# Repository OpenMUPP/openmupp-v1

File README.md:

# OpenMUPP v1 probe board

OpenMUPP v1 is a multi-protocol programming and debug probe.
The design is open hardware.
The board name is `OpenMUPP v1`.
The KiCad 10 project is in this repository.

## What the board does

- It runs **USB CDC, CMSIS-DAP v2 and EDBG (AVR) at the same time** in one firmware image.
- It transfers data **faster than the original Versaloon Mini**. The core runs at 144 MHz, and USB runs at high speed (480 Mbit/s).
- It connects to targets from **1.2 V to 5 V** through level shifters. A 1.2 V target is limited to about 5 MHz.
- It supplies the target with **3.3 V or 5 V (up to about 300 mA)**.
- It makes an adjustable **VPP of 5 V to 14 V** for high-voltage programming of AVR and PIC parts.
- It has **one target connector (J4)**. An adapter board plugs onto J4 and maps it to each target pinout.

## Hardware overview

```mermaid
flowchart LR
    usb["USB-C (J1)"] --> fuse["Polyfuse F1<br/>1.1 A<br/>+5V"]
    fuse --> ldo["3.3 V LDO"]
    fuse --> boost["Boost (U13)<br/>5 V to 14 V"]
    ldo --> mcu["CH32V307RCT6 (U2)<br/>3.3 V"]
    mcu <--> ls["Level shifters<br/>U3 to U6"]
    ls --> esd["33 Ω series resistors<br/>and ESD diodes"]
    esd --> j4["Target connector J4<br/>2 × 10, 2.54 mm"]

    ldo --> tps33["3.3 V target switch<br/>TPS2553 (U12)"]
    fuse --> tps5["5 V target switch<br/>TPS2553 (U14)"]
    tps33 --> vtref(("VTREF"))
    tps5 --> vtref
    vtref --> j4

    boost --> vpp["VPP switch<br/>P-FET (Q2)"]
    vpp --> j4
    pd["Pin 19 pull-down<br/>N-FET (Q6), pull-up to VTREF"] --> j4

    mcu -- "TARGET_PWR_EN" --> tps33
    mcu -- "TARGET_5V_EN" --> tps5
    mcu -- "VPP_12V_ADJ<br/>(DAC: 5 V to 14 V)" --> boost
    mcu -- "VPP_EN, VPP_ON" --> vpp
    mcu -- "VPP_PD" --> pd
    boost -- "VPP_SENSE" --> mcu
```

| Block | Part | Notes |
|-------|------|-------|
| MCU | CH32V307RCT6, LQFP64 (U2) | QingKe V4F RISC-V, 144 MHz, 256 KB flash, 64 KB SRAM. 8 MHz crystal (Y1). |
| USB | USB-C receptacle (J1), USBLC6-2SC6 (U1) | USB 2.0 high speed (USBHS on PB6, PB7). 5.1 kΩ CC resistors. |
| 3.3 V rail | XC6220B331MR-G LDO | Supplies the MCU and the target power switch. |
| VBUS protection | 1.1 A polyfuse (F1), 2.2 A trip, 16 V | At 4.75 V VBUS, expect `+5V` at about 4.6 V or more at full load. See [Target power](docs/hardware.md#target-power). |
| Target power (3.3 V or 5 V) | TPS2553 (U12, 3.3 V), TPS2553 (U14, 5 V), FDV301N interlock (Q4) | Current limit about 300 mA (ILIM 91 kΩ) on each rail. Both outputs join `VTREF`. See [Target power](docs/hardware.md#target-power). |
| VPP (5 V to 14 V) | MT3608 boost (U13), AO3401A P-FET (Q2), FDV301N driver (Q3), MMBT3906 current limit (Q5), FDV301N pull-down (Q6) | The firmware sets the level with the DAC on PA5 (`VPP_12V_ADJ`). Current limit about 17 mA. Pin 19 has three states: 0 V, `VTREF` and VPP. See [High voltage (VPP)](docs/hardware.md#high-voltage-vpp). |
| Level shifters | SN74LXC8T245 (U3, U4), SN74LXC1T45 (U5, U6) | All parts work from 1.1 V to 5.5 V. |
| Reset path | FDV301N (Q1), U4 channel 4 | Q1 pulls nRESET low. U4 reads the line back. |
| ESD | TPD4E05U06 (U8 to U10) | On all J4 signals except the supplies. |
| Probe debug | J3 (5-pin SWD), J2 (4-pin UART) | J3 debugs the probe MCU only. J2 is the log port of the probe firmware. **They are not target connectors.** |
| User I/O | SW1 (key and BOOT0), LEDs D1 (blue) and D4 (red) for state, D2 (green) for USB | |

### Target connector J4

J4 is a 2 × 10 IDC header, 2.54 mm. The footprint in the schematic is `Connector_IDC:IDC-Header_2x10_P2.54mm_Horizontal`. Use a shrouded and keyed header. VPP is on pin 19, so a shifted plug must not fit.

| Pin | Signal | Pin | Signal |
|-----|--------|-----|--------|
| 1 | `VTREF`: target voltage sense, and target supply when the probe powers the target | 2 | Reserved (no connect) |
| 3 | GND | 4 | TMS / SWDIO / data (`DIR_SWDIO`) |
| 5 | GND | 6 | TCK / SWCLK / SCK |
| 7 | GND | 8 | TDO / SWO / MISO |
| 9 | GND | 10 | TDI / MOSI |
| 11 | RTCK | 12 | nRESET / debugWIRE, open-drain |
| 13 | UART TX (probe output) | 14 | UART RX (probe input) |
| 15 | TRST | 16 | Adapter ID (ADC, 3.3 V domain) |
| 17 | `AUX1` | 18 | `AUX2` |
| 19 | VPP (0 V, `VTREF`, or 5 V to 14 V) | 20 | GND |

- **Target power is on pin 1.** One pin carries the sense and the supply. The limit is about 300 mA at 3.3 V and at 5 V.
- **Pin 2 is reserved.** A later adapter that needs a second supply pin can use it, with its own switch.
- **Pin 16 goes to the adapter only.** It never goes to the target.

### Adapter boards and adapter ID

An adapter board has connectors, wires and one ID resistor. The resistor goes from J4 pin 16 to GND. R30 (10 kΩ) pulls pin 16 up to 3.3 V. The firmware reads the ratio x = R<sub>ID</sub> / (R<sub>ID</sub> + 10 kΩ) on PB1. The ADC reference and R30 share the 3.3 V rail, so supply drift cancels. R44 (10 kΩ) in series and D5 (BAT54 Schottky diode) to 3.3 V protect PB1 (net `ADAPTER_ID_MCU`). They work when a 5 V target supply is on pin 16 by mistake. C13 (100 nF) from `ADAPTER_ID_MCU` to GND filters the ADC input. The firmware must use a long ADC sample time and keep the internal pull resistors off.

The AVR 10-pin connector uses the Atmel-ICE pinout. Three passive variants route the data pin to SWDIO:

| Variant | Protocols | Slot |
|---------|-----------|------|
| A | JTAG, ISP, debugWIRE | 1 |
| B | PDI | 2 |
| C | TPI, aWire | 3 |

UPDI does not use SWDIO. It uses J4 pin 12 (nRESET), because the 2.2 kΩ pull-up on SWDIO is too strong for the UPDI pin of the target. See [adapters/README.md](adapters/README.md#updi-on-j4-pin-12). A UPDI adapter variant for the Atmel-ICE 10-pin connector has no slot yet.

| Slot | R<sub>ID</sub> (E24, 1 %) | x | Accept window | Use |
|------|------------------|-------|---------------|-----|
| — | 0 Ω (short) | 0.000 | below 0.05 | Fault: pin 16 shorted to GND |
| 1 | 1.1 kΩ | 0.099 | 0.05 to 0.15 | Variant A |
| 2 | 2.4 kΩ | 0.194 | 0.15 to 0.25 | Variant B |
| 3 | 4.3 kΩ | 0.301 | 0.25 to 0.35 | Variant C |
| 4 | 6.8 kΩ | 0.405 | 0.35 to 0.45 | Arm adapter |
| 5 | 10 kΩ | 0.500 | 0.45 to 0.55 | Pin-header adapter |
| 6 | 15 kΩ | 0.600 | 0.55 to 0.65 | Free |
| 7 | 24 kΩ | 0.706 | 0.65 to 0.75 | Free |
| 8 | 39 kΩ | 0.796 | 0.75 to 0.85 | AVR high-voltage adapter |
| 9 | 91 kΩ | 0.901 | 0.85 to 0.95 | PIC high-voltage adapter |
| — | open | 1.000 | above 0.95 | No adapter |

The worst-case error is about 0.007 in x, and the windows are ±0.05 wide. The firmware treats a free slot as "unknown adapter". The firmware enables VPP only for slots 8 and 9.

The adapter schematics are in [adapters/](adapters/README.md). Each adapter has a female 2 × 10 header that plugs directly onto J4. No ribbon cable is necessary.

See [docs/hardware.md](docs/hardware.md) for the sheets, level shifting, target power, VPP and the MCU pin map.

## Firmware

The firmware is the `openmupp` project. The CH32V307 has a ROM bootloader. It can program the flash through USB (WCH ISP protocol). The bootloader can also use USART1 (PA9, PA10), but on this board these pins drive LEDs and have no connector. Hold SW1 (BOOT0) during reset to start it. The firmware port to the CH32V307 is in progress. A firmware jump to the bootloader is not available yet.

Related repositories:

- Firmware: <https://github.com/OpenMUPP/openmupp>
- Drivers: <https://github.com/armint/ch32v00x-system> and <https://github.com/armint/ch32v00x-art>

## Getting started

### Requirements

- KiCad 10.0.6 or newer.
- The shared footprint libraries. They are not public. The PCB file has a copy of each footprint, so you can open and edit the board without them. The project uses the nicknames `resistors`, `capacitors`, `headers`, `connectors`, `inductors` and `sot`. The stock KiCad libraries (`Package_*`, `Connector_IDC`, `Diode_SMD`, `LED_SMD`, `Crystal`, `Fuse`, `Button_Switch_SMD`) must also be present.

### Open the project

1. Clone this repository.
2. Open `openmupp-v1.kicad_pro`.

The board and the schematic open without the shared footprint libraries. To change a footprint, edit the copy in the PCB file.

The project symbol library `openmupp-v1` is in the repository. `sym-lib-table` links it with `${KIPRJMOD}`.

### Conventions

- **Reference designators are unique across all sheets.** Check before you add a part.
- **Every part has an `LCSC` field** for JLCPCB assembly. Prefer parts from the JLCPCB basic library. Each extended part costs a setup fee.
- **Small N-FETs:** use the FDV301N (LCSC C15310). V<sub>GS(th)</sub> is 1.06 V maximum, so a gate drive of 1.8 V turns it on. The limits are 25 V V<sub>DS</sub> and 8 V V<sub>GS</sub>.
- **Footprints:** check the pads against the datasheet land pattern.
- **Checks:** run ERC after each change. Look for shorted nets and for unconnected pins.

## License

Copyright Armin van der Togt 2026.

This design is licensed under the CERN Open Hardware Licence Version 2 - Strongly Reciprocal (CERN-OHL-S-2.0). See [LICENSE](LICENSE).
The design has no warranty. Refer to the licence for the applicable conditions.

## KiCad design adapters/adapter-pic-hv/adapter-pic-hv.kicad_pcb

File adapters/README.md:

# Target adapters for OpenMUPP v1

Each folder is a KiCad 10 project with the schematic and the board layout of one target adapter.

| Folder                                     | Adapter          | Slot | R<sub>ID</sub> | Target connectors                                              |
|--------------------------------------------|------------------|------|----------------|----------------------------------------------------------------|
| [adapter-avr-jtag-isp](adapter-avr-jtag-isp/) | AVR variant A | 1 | 1.1 kΩ | Atmel-ICE 10 (1.27 mm), AVR JTAG 10 (2.54 mm), 2 × 3 ISP |
| [adapter-arm](adapter-arm/)                | Arm              | 4    | 6.8 kΩ         | ARM JTAG 20, Cortex Debug 10, STDC14                           |
| [adapter-pin-header](adapter-pin-header/)  | Pin header       | 5    | 10 kΩ          | 1 × 6 SWD / CH32 / SWIM, 1 × 4 ST SWIM, 2 × 5 WCH-LinkE layout |
| [adapter-avr-hv](adapter-avr-hv/)          | AVR high voltage | 8    | 39 kΩ          | DIP-8 and DIP-14 sockets (HVSP), 2 × 3 TPI and UPDI            |
| [adapter-pic-hv](adapter-pic-hv/)          | PIC high voltage | 9    | 91 kΩ          | PICkit ICSP 1 × 6                                              |

The slot table and the J4 pinout are in the [main README](../README.md#adapter-boards-and-adapter-id).

## Rules for all adapters

1. J1 is a female 2 × 10 header, 2.54 mm. It plugs directly onto J4 of the probe. The pin numbers of J1 are the J4 pin numbers.
2. One 1 % resistor (R1) goes from J1 pin 16 to GND. J1 pin 16 never goes to the target.
3. J1 pin 2 (reserved) stays open. J1 pin 19 (VPP) stays open on each adapter that is not a high-voltage adapter.
4. Each adapter has a 1 × 4 debug UART header (J5): 1 GND, 2 RX (probe input), 3 TX (probe output), 4 `VTREF`. The labels are from the probe side. Pins 1 to 3 have the same order as J2 on the main board. Pin 4 lets the UART work without a debug connector to the target.
5. Connect only one target connector at a time.

## Female header on J4

J4 on the probe is a shrouded, right-angle header (`IDC-Header_2x10_P2.54mm_Horizontal`). The adapter boards use `PinSocket_2x10_P2.54mm_Horizontal` for J1, so the adapter board is in the same plane as the probe. Check these items before you order the boards:

- **Fit.** The socket body must go into the shroud of J4. Measure the shroud opening and the socket body.
- **Pin mirror.** The socket and the header mate face to face. Make sure that J1 pin 1 touches J4 pin 1 in the layout.
- **Polarity.** A plain socket has no key, so it can go in rotated by 180°. Then J1 pin 16 touches a probe GND pin, and the probe pin 16 touches an adapter GND pin. The adapter ID reads 0 Ω (the fault slot). The firmware must then keep the shifter outputs, the target power and VPP off. Use a keyed socket, or add a mechanical key on the adapter board, if possible.

## RESET and MCLR on J4 pin 19

`adapter-avr-hv` and `adapter-pic-hv` connect the target RESET or MCLR pin directly to J1 pin 19. The nets are `RESET_VPP` and `MCLR_VPP`. The probe gives pin 19 three levels: 0 V (reset), `VTREF` (run) and VPP (program). See [Pin 19 states](../docs/hardware.md#pin-19-states). Thus the adapters have no reset circuit, and J1 pin 18 (`AUX2`) is not used.

HVSP entry needs RESET at 0 V while `VCC` comes up. Then RESET must go to 12 V after a short time. Q6 on the probe holds pin 19 at 0 V. The firmware can set `VPP_ON` before `VCC` comes up, because Q6 holds pin 19 low against the current limit. Then the firmware releases Q6 at the time that the data sheet gives. Pin 19 then goes to VPP in some µs.

## UPDI on J4 pin 12

UPDI uses J4 pin 12 (nRESET / debugWIRE), not J4 pin 4 (SWDIO). The reasons:

- The UPDI pin of a tinyAVR is a weak driver. The ATtiny1614/16/17 data sheet (DS40002204A, table 36-16, VOL2) guarantees only 0.1 mA at 1.8 V and 0.5 mA at 5 V.
- J4 pin 4 has a 2.2 kΩ pull-up on the probe. The target must then sink 0.8 mA to 2.3 mA. See issue [#6](https://github.com/OpenMUPP/openmupp-v1/issues/6).
- J4 pin 12 has a 10 kΩ pull-up. The target must sink 0.18 mA at 1.8 V and 0.5 mA at 5 V.
- J4 pin 12 is open-drain (Q1 on the probe). This is the physical layer that UPDI expects.

Effects on the firmware:

- The read-back of J4 pin 12 goes to PB11 (USART3_RX). The USART receives UPDI and sees its own transmit.
- The CH32V307 USART cannot invert TX, so the firmware sends UPDI in software through Q1 (PB12). debugWIRE uses the same method.
- The rise time with 10 kΩ and about 30 pF to 50 pF is about 0.3 µs to 0.5 µs. This is sufficient for 225 kbps (the maximum UPDI rate at 1.8 V). It is not sufficient for 0.9 Mbps. These values are estimates, not measurements.
- The debug UART (J4 pins 13 and 14) stays free during UPDI.

On `adapter-avr-hv`, TPI data also uses J4 pin 12, through the same path as UPDI. The TPIDATA pin of the ATtiny4/5/9/10 has an internal pull-up in TPI mode (20 kΩ to 50 kΩ). The target drives a 0 and the first 1 of a sequence. Then the pull-up holds the line high (ATtiny4/5/9/10 data sheet DS40002060A, section 15.3.8). Thus TPI and UPDI see the same physical layer: open drain with a pull-up. Other TPI adapters can still use J4 pin 4.

## UPDI high-voltage pulse

`adapter-avr-hv` has one 2 × 3 header (J4) for TPI and UPDI. JP1, a 2-pin jumper header, selects the pin that gets the high voltage (HV):

| JP1 | Use | Pin 1 (data) | Pin 5 | HV goes to |
|-----|-----|--------------|-------|------------|
| Open | TPI (ATtiny4/5/9/10). UPDI with a separate RESET pin, for example AVR DD. | `UPDI_HV` (through Q2 to J1 pin 12) | `RESET_VPP` (J1 pin 19) | Pin 5 |
| Closed | UPDI with HV on the UPDI pin (tinyAVR 0, 1 and 2 series) | `UPDI_HV` (through Q2 to J1 pin 12) | `RESET_VPP` (J1 pin 19) | Pin 1 and pin 5 |

On the tinyAVR 0, 1 and 2 series, the UPDI pin and the RESET pin are the same pin. The data sheet calls the HV entry "UPDI Enable with High-Voltage Override of RESET Pin". The HV detection level (V<sub>HVRST</sub>) is 11.5 V to 12.5 V. The AVR DD setting is not verified against a part. Check the data sheet of each part before you use it.

The TPIDATA pin and the AVR DD UPDI pin must not get 12 V. Thus JP1 must be open for these parts. With JP1 closed, pin 5 also gets VPP. On a tinyAVR target board, pin 5 is usually not connected, so this is permitted. Some target boards connect pin 5 to the UPDI pin. Then pin 19 at 0 V holds the UPDI line low. Check the target board before you use it.

The parts of the UPDI path:

1. D1 (BAT54A) and JP1 connect J1 pin 19 to `UPDI_HV` when JP1 is closed. D1 has a drop of about 0.3 V. Set VPP to about 12.3 V for 12 V on the UPDI pin. `RESET_VPP` has no diode, so it gets VPP directly.
2. Q2 (FDV301N) is a pass switch between `UPDI_HV` (drain) and `UPDI` (source, J1 pin 12). The gate is on `VTREF`. When `UPDI_HV` is at 12 V, Q2 is off and the 10 kΩ pull-up on the probe holds `UPDI` at `VTREF`. The body diode is then reverse biased. The ESD diode on J4 pin 12 of the probe clamps at about 6 V, so this protection is necessary.
3. While VPP is off, Q2 passes UPDI and TPI data in both directions. The probe pulls `UPDI` high (10 kΩ). The internal pull-up of the target pulls `UPDI_HV` high. The adapter has no pull-up on `UPDI_HV`, so it adds no load to the weak UPDI pad.
4. With JP1 closed, keep pin 19 at 0 V (`VPP_PD` high) during UPDI, except during the HV pulse. In the run state, pin 19 is at `VTREF`. Then R39 on the probe and D1 pull `UPDI_HV` up. When the target sends a 0, it must also sink this current: about 0.13 mA at 1.8 V and 0.45 mA at 5 V. The UPDI pad guarantees only 0.1 mA at 1.8 V. At 0 V on pin 19, D1 blocks and adds no load.
5. The firmware can read the JP1 position before it sets VPP on. Put pin 19 in the run state and set Q1 on. With JP1 closed, current flows from R39 through D1, Q2 and Q1. `VPP_SENSE2` then reads less than about 0.5 V. With JP1 open, `VPP_SENSE2` reads the run level. If the JP1 position does not agree with the selected target, the firmware must not set VPP on. This value is an estimate, not a measurement.

Limits:

- Q2 passes a low level only when `VTREF` is above V<sub>GS(th)</sub>. The FDV301N has 1.06 V maximum, so `VTREF` of 1.8 V is sufficient. The tinyAVR parts run from 1.8 V to 5.5 V.
- The gate-source voltage of the FDV301N must stay above −0.3 V. The source (`UPDI`) has a 10 kΩ pull-up to the gate potential (`VTREF`), so it does not go above the gate. Q2 leakage (I<sub>DSS</sub> 1 µA maximum at 20 V) moves `UPDI` by about 10 mV.
- A low-to-high edge on `UPDI_HV` above `VTREF` − V<sub>GS(th)</sub> comes from the target pull-up only. This is slower than on `UPDI`. Check the rise time at the UPDI baud rate and at the TPI clock rate.
- VPP goes to `RESET_VPP`. With JP1 closed, it also goes to `UPDI_HV` at the same time. Connect only one target to J2, J3 or J4.
- After the pulse, the line must return to the normal level quickly: the debugger drives it low 1 µs to 10 µs after the HV ends (data sheet figure 33-6). D1 cannot pull `UPDI_HV` down. The probe pulls J4 pin 12 low through its Q1. The adapter Q2 then conducts, because its gate is at `VTREF`, and pulls `UPDI_HV` low. At the same time, Q6 on the probe pulls pin 19 to 0 V in less than 1 µs, so D1 blocks at once.
- The TPS2553 on the probe has a soft start of some milliseconds. Check the pulse timing in the target data sheet.

## HVSP pull-downs

HVSP entry needs the three Prog_enable pins at 0 while `VCC` comes up. R4 to R7 (10 kΩ) hold them low on `adapter-avr-hv`. These resistors are not in the adapter plan. The pins come from the ATtiny datasheets:

| Part              | Prog_enable[0..2]           | Resistors                                          |
|-------------------|-----------------------------|----------------------------------------------------|
| ATtiny13/25/45/85 | SDI, SII, SDO (PB0 to PB2)  | The probe drives SDI and SII low. R4 holds SDO low |
| ATtiny24A/44A/84A | PA0, PA1, PA2 (pins 13, 12, 11) | R5, R6, R7                                     |

J4 pin 8 (SDO input) is an input only, so the probe cannot hold SDO low. The target drives SDO against R4 after entry.

## Items to check before production

- **WCH-LinkE layout.** The positions of GND, 3V3 and 5V on the WCH-LinkE header come from the schematic text only. Check them on a real WCH-LinkE. Pin 8 (3V3) connects to `VTREF`. Pin 10 (5V) stays open.
- **ST SWIM order.** Check the order (VDD, SWIM, GND, NRST) against ST UM1075.
- **1.27 mm headers.** Cortex Debug 10 and STDC14 use plain 1.27 mm pin headers in the schematic. Use shrouded, keyed parts (Samtec FTSH-105 and FTSH-107, or equal). Put their footprints in the `kicad-footprints` repository.
- **Atmel-ICE 10.** J2 on `adapter-avr-jtag-isp` is a plain 1.27 mm pin header in the schematic. Use a shrouded, keyed part, as for Cortex Debug 10. J4 (AVR JTAG 10, 2.54 mm) uses a shrouded IDC header.
- **Footprint libraries.** All resistors are 0603 and use `resistors:R_0603` from the `kicad-footprints` repository, as on the main board.

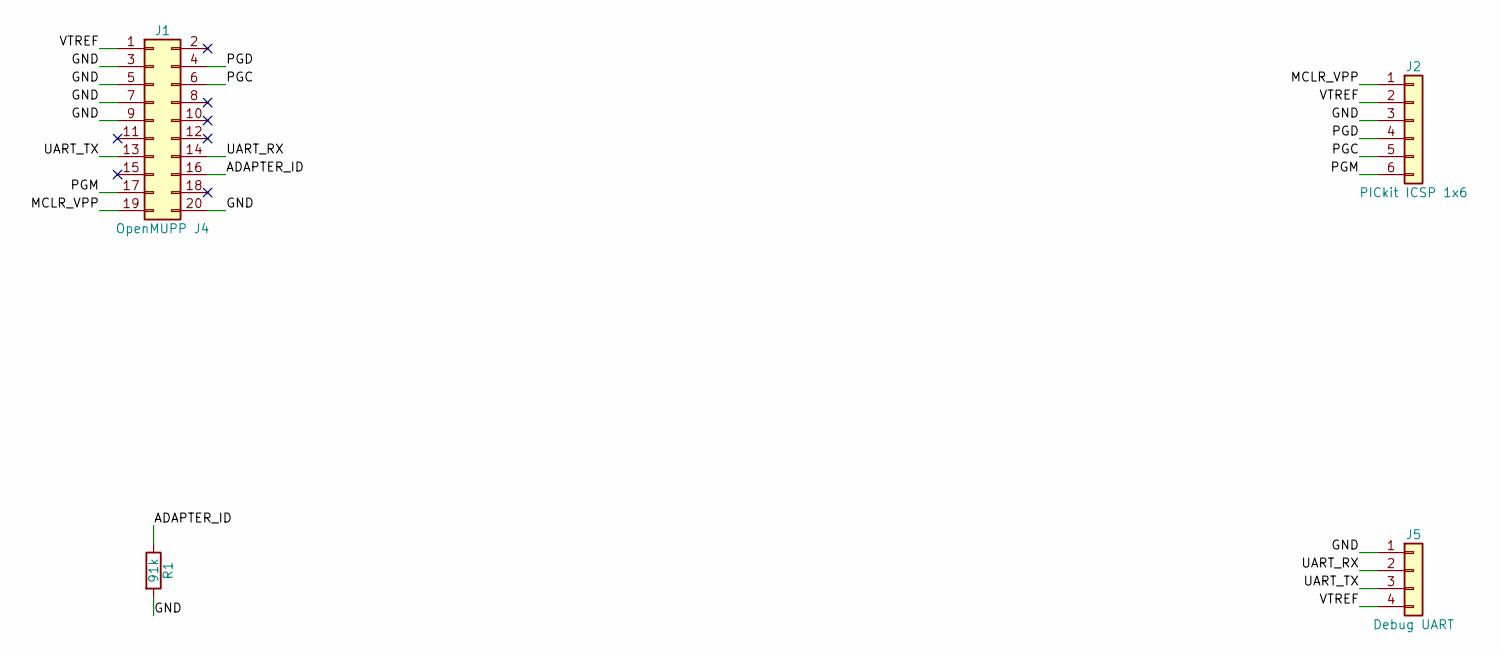
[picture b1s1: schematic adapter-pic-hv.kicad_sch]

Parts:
J1: OpenMUPP J4; PinSocket_2x10_P2.54mm_Horizontal
J2: PICkit ICSP 1x6; PinHeader_1x06_P2.54mm_Vertical
J5: Debug UART; PinHeader_1x04_P2.54mm_Vertical
R1: 91k; R_0603

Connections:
/ADAPTER_ID: J1.16, R1.1
/GND: J1.3, J1.5, J1.7, J1.9, J1.20, J2.3, J5.1, R1.2
/MCLR_VPP: J1.19, J2.1
/PGC: J1.6, J2.5
/PGD: J1.4, J2.4
/PGM: J1.17, J2.6
/UART_RX: J1.14, J5.2
/UART_TX: J1.13, J5.3
/VTREF: J1.1, J2.2, J5.4

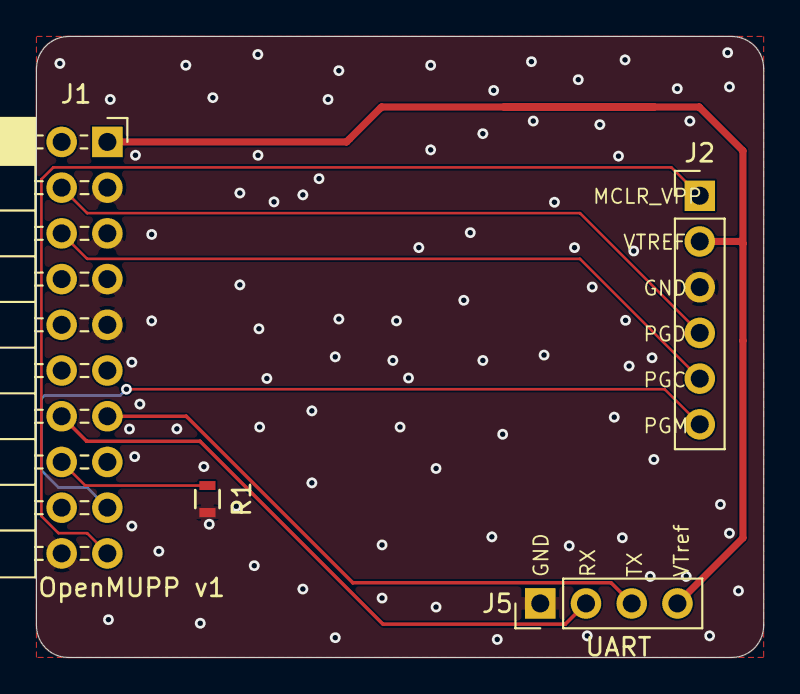
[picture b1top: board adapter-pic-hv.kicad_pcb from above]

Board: 2 copper layers, 40.4 x 34.5 mm, 4 parts (0 on the bottom side), 9 nets.

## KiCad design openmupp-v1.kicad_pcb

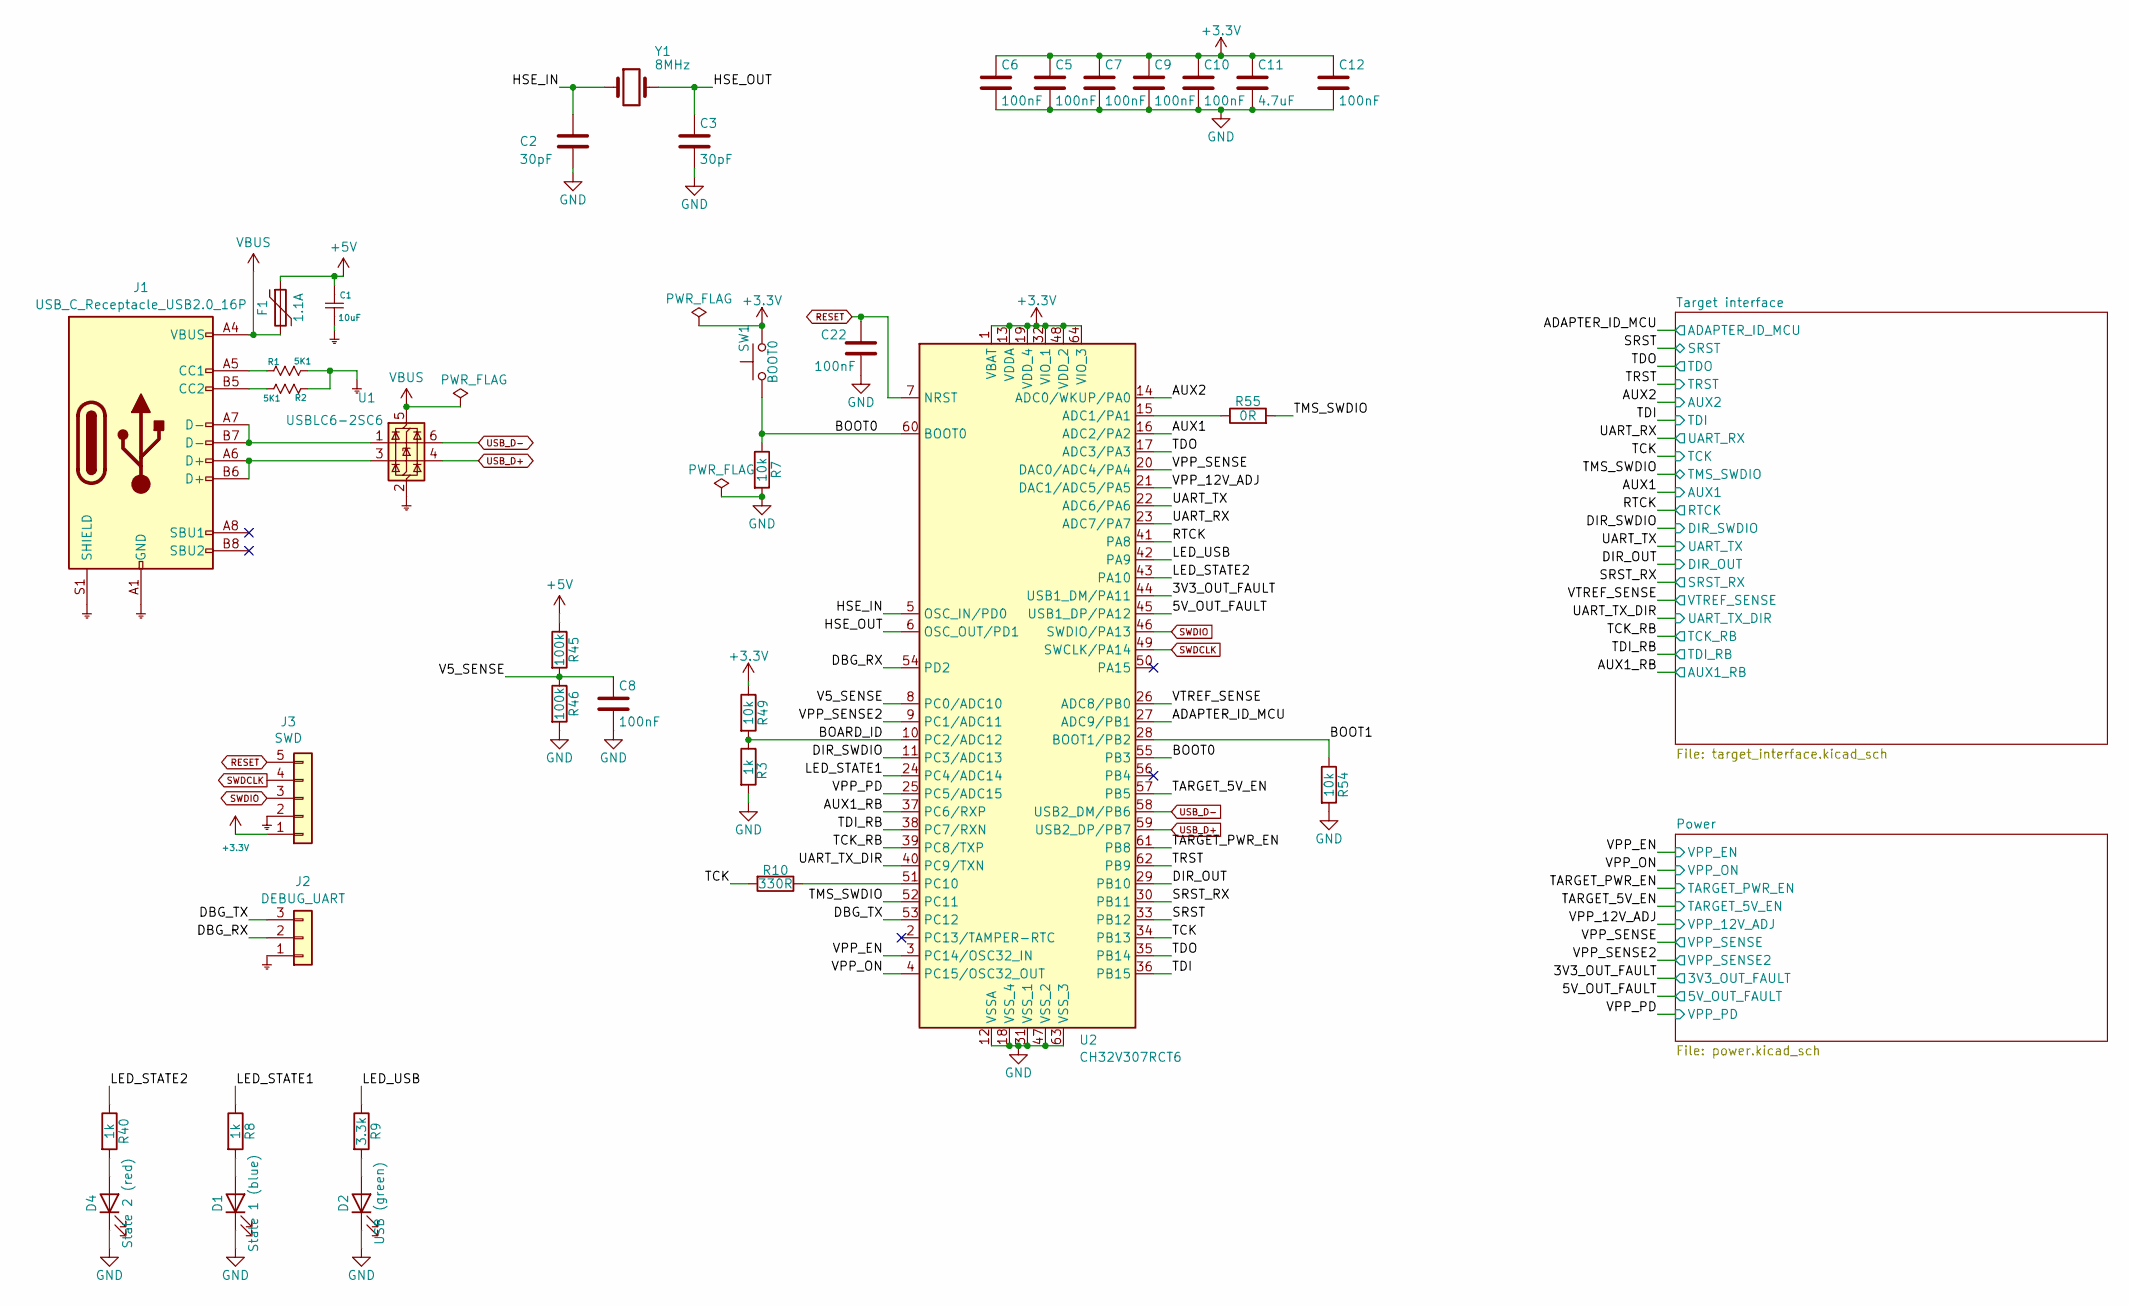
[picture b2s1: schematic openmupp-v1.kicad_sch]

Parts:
C1: 10uF; C_1206; VoltageRating 50V; LCSC C13585
C2, C3: 30pF; C_0402_1005Metric; LCSC C1570
C5, C6, C7, C8, C9, C10, C12, C22: 100nF; C_0603; LCSC C14663
C11: 4.7uF; C_0603; LCSC C19666
D1: State 1 (blue); LED_0603_1608Metric; LCSC C2288
D2: USB (green); LED_0603_1608Metric; LCSC C12624
D4: State 2 (red); LED_0603_1608Metric; LCSC C2286
F1: 1.1A; Fuse_1206_3216Metric; LCSC C7542961
J1: USB_C_Receptacle_USB2.0_16P; USB_C_Receptacle_HRO_TYPE-C-31-M-12; LCSC C165948
J2: DEBUG_UART; PinHeader_1x03_P2.54mm_Vertical
J3: SWD; PinHeader_1x05_P2.54mm_Vertical
R1, R2: 5K1; R_0402; LCSC C25905
R3, R8, R40: 1k; R_0402; LCSC C11702
R7, R49, R54: 10k; R_0402; LCSC C25744
R9: 3.3k; R_0402; LCSC C25890
R10: 330R; R_0603; LCSC C25104
R45, R46: 100k; R_0402; LCSC C25741
R55: 0R; R_0603; LCSC C17168
SW1: BOOT0; SW_Push_HanElectricity_TS1109_4.5x4.5mm_H3.8mm; LCSC C22375347
U1: USBLC6-2SC6; SOT-23-6; LCSC C7519
U2: CH32V307RCT6; TQFP-64_10x10mm_P0.5mm; LCSC C2988083
Y1: 8MHz; Crystal_SMD_5032-2Pin_5.0x3.2mm; MPN X50328MSB2GI; LCSC C115962

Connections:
/3V3_OUT_FAULT: U2.44 (USB1_DM/PA11); also elsewhere on the board
/5V_OUT_FAULT: U2.45 (USB1_DP/PA12); also elsewhere on the board
/ADAPTER_ID_MCU: U2.27 (ADC9/PB1); also elsewhere on the board
/AUX1: U2.16 (ADC2/PA2); also elsewhere on the board
/AUX1_RB: U2.39 (PC8/TXP); also elsewhere on the board
/AUX2: U2.14 (ADC0/WKUP/PA0); also elsewhere on the board
/BOARD_ID: R3.1, R49.2, U2.10 (PC2/ADC12)
/BOOT0: R7.1, SW1.1, U2.55 (PB3), U2.60 (BOOT0)
/BOOT1: R54.1, U2.28 (BOOT1/PB2)
/DBG_RX: J2.2, U2.54 (PD2)
/DBG_TX: J2.3, U2.53 (PC12)
/DIR_OUT: U2.29 (PB10); also elsewhere on the board
/DIR_SWDIO: U2.11 (PC3/ADC13); also elsewhere on the board
/HSE_IN: C2.1, U2.5 (OSC_IN/PD0), Y1.1
/HSE_OUT: C3.1, U2.6 (OSC_OUT/PD1), Y1.2
/LED_STATE1: R8.1, U2.24 (PC4/ADC14)
/LED_STATE2: R40.1, U2.43 (PA10)
/LED_USB: R9.1, U2.42 (PA9)
/RTCK: U2.41 (PA8); also elsewhere on the board
/SRST: U2.33 (PB12); also elsewhere on the board
/SRST_RX: U2.30 (PB11); also elsewhere on the board
/TARGET_5V_EN: U2.57 (PB5); also elsewhere on the board
/TARGET_PWR_EN: U2.61 (PB8); also elsewhere on the board
/TCK_RB: U2.37 (PC6/RXP); also elsewhere on the board
/TDI: U2.36 (PB15); also elsewhere on the board
/TDI_RB: U2.38 (PC7/RXN); also elsewhere on the board
/TDO: U2.17 (ADC3/PA3), U2.35 (PB14); also elsewhere on the board
/TMS_SWDIO: R55.2, U2.52 (PC11); also elsewhere on the board
/TRST: U2.62 (PB9); also elsewhere on the board
/UART_RX: U2.23 (ADC7/PA7); also elsewhere on the board
/UART_TX: U2.22 (ADC6/PA6); also elsewhere on the board
/UART_TX_DIR: U2.40 (PC9/TXN); also elsewhere on the board
/V5_SENSE: C8.1, R45.2, R46.1, U2.8 (PC0/ADC10)
/VPP_12V_ADJ: U2.21 (DAC1/ADC5/PA5); also elsewhere on the board
/VPP_EN: U2.3 (PC14/OSC32_IN); also elsewhere on the board
/VPP_ON: U2.4 (PC15/OSC32_OUT); also elsewhere on the board
/VPP_PD: U2.25 (PC5/ADC15); also elsewhere on the board
/VPP_SENSE: U2.20 (DAC0/ADC4/PA4); also elsewhere on the board
/VPP_SENSE2: U2.9 (PC1/ADC11); also elsewhere on the board
/VTREF_SENSE: U2.26 (ADC8/PB0); also elsewhere on the board
unnamed: D1.2 (A), R8.2
unnamed: D2.2 (A), R9.2
unnamed: D4.2 (A), R40.2
unnamed: J1.A5 (CC1), R1.1
unnamed: J1.B5 (CC2), R2.2
unnamed: J1.A6 (D+), J1.B6 (D+), U1.3 (I/O2)
unnamed: J1.A7 (D-), J1.B7 (D-), U1.1 (I/O1)
unnamed: R55.1, U2.15 (ADC1/PA1)
RESET: C22.1, J3.5, U2.7 (NRST)
SWDCLK: J3.4, U2.49 (SWCLK/PA14)
SWDIO: J3.3, U2.46 (SWDIO/PA13)
USB_D+: U1.4 (I/O2), U2.59 (USB2_DP/PB7)
USB_D-: U1.6 (I/O1), U2.58 (USB2_DM/PB6)

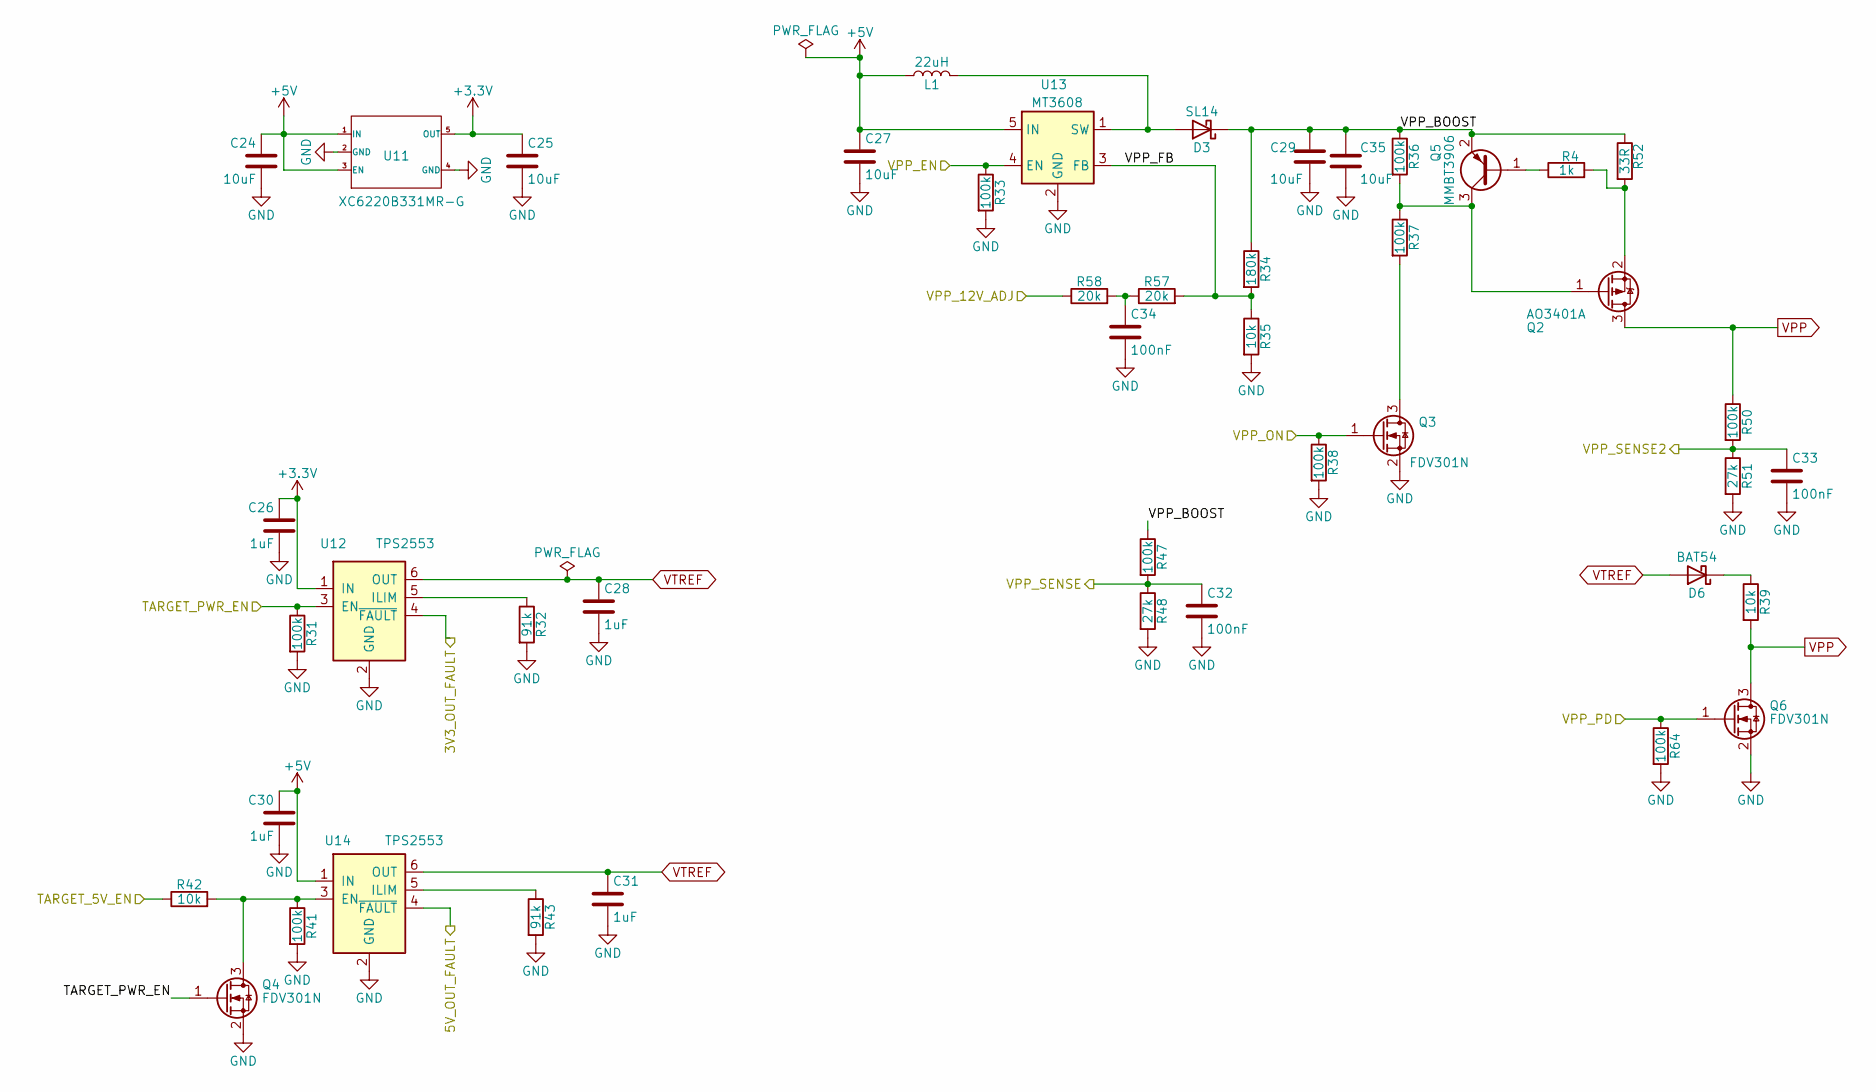
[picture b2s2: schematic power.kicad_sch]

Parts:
C24, C25: 10uF; C_1206; LCSC C13585
C26, C28, C30, C31: 1uF; C_0603; LCSC C15849
C27, C29, C35: 10uF; C_0805; LCSC C15850
C32, C33, C34: 100nF; C_0603; LCSC C14663
D3: SL14; D_SOD-123; LCSC C698818
D6: BAT54; D_SOD-323; LCSC C21107
L1: 22uH; L_FNR5040S; LCSC C167971
Q2: AO3401A; SOT-23; LCSC C15127
Q3, Q4, Q6: FDV301N; SOT-23; LCSC C15310
Q5: MMBT3906; SOT-23; LCSC C2940
R4: 1k; R_0402; LCSC C11702
R31, R33, R36, R37, R38, R41, R47, R50, R64: 100k; R_0402; LCSC C25741
R32, R43: 91k; R_0603; LCSC C23265
R34: 180k; R_0402; LCSC C25760
R35, R39, R42: 10k; R_0402; LCSC C25744
R48, R51: 27k; R_0402; LCSC C25771
R52: 33R; R_0402; LCSC C25105
R57, R58: 20k; R_0402; LCSC C25765
U11: XC6220B331MR-G; SOT23_5L; LCSC C3040644
U12, U14: TPS2553; SOT-23-6; LCSC C111738
U13: MT3608; SOT23_6L; LCSC C84817

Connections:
/3V3_OUT_FAULT: U12.4 (~FAULT); also elsewhere on the board
/5V_OUT_FAULT: U14.4 (~FAULT); also elsewhere on the board
/Power/VPP_BOOST: C29.1, C35.1, D3.1 (K), Q5.2 (E), R34.1, R36.1, R47.1, R52.1
/Power/VPP_FB: R34.2, R35.1, R57.2, U13.3 (FB)
/TARGET_5V_EN: R42.1; also elsewhere on the board
/TARGET_PWR_EN: Q4.1 (G), R31.1, U12.3 (EN); also elsewhere on the board
/VPP_12V_ADJ: R58.1; also elsewhere on the board
/VPP_EN: R33.1, U13.4 (EN); also elsewhere on the board
/VPP_ON: Q3.1 (G), R38.1; also elsewhere on the board
/VPP_PD: Q6.1 (G), R64.1; also elsewhere on the board
/VPP_SENSE: C32.1, R47.2, R48.1; also elsewhere on the board
/VPP_SENSE2: C33.1, R50.2, R51.1; also elsewhere on the board
unnamed: C34.1, R57.1, R58.2
unnamed: D3.2 (A), L1.2, U13.1 (SW)
unnamed: D6.1 (K), R39.1
unnamed: Q2.1 (G), Q5.3 (C), R36.2, R37.1
unnamed: Q2.2 (S), R4.2, R52.2
unnamed: Q3.3 (D), R37.2
unnamed: Q4.3 (D), R41.1, R42.2, U14.3 (EN)
unnamed: Q5.1 (B), R4.1
unnamed: R32.1, U12.5 (ILIM)
unnamed: R43.1, U14.5 (ILIM)
VPP: Q2.3 (D), Q6.3 (D), R39.2, R50.1; also elsewhere on the board

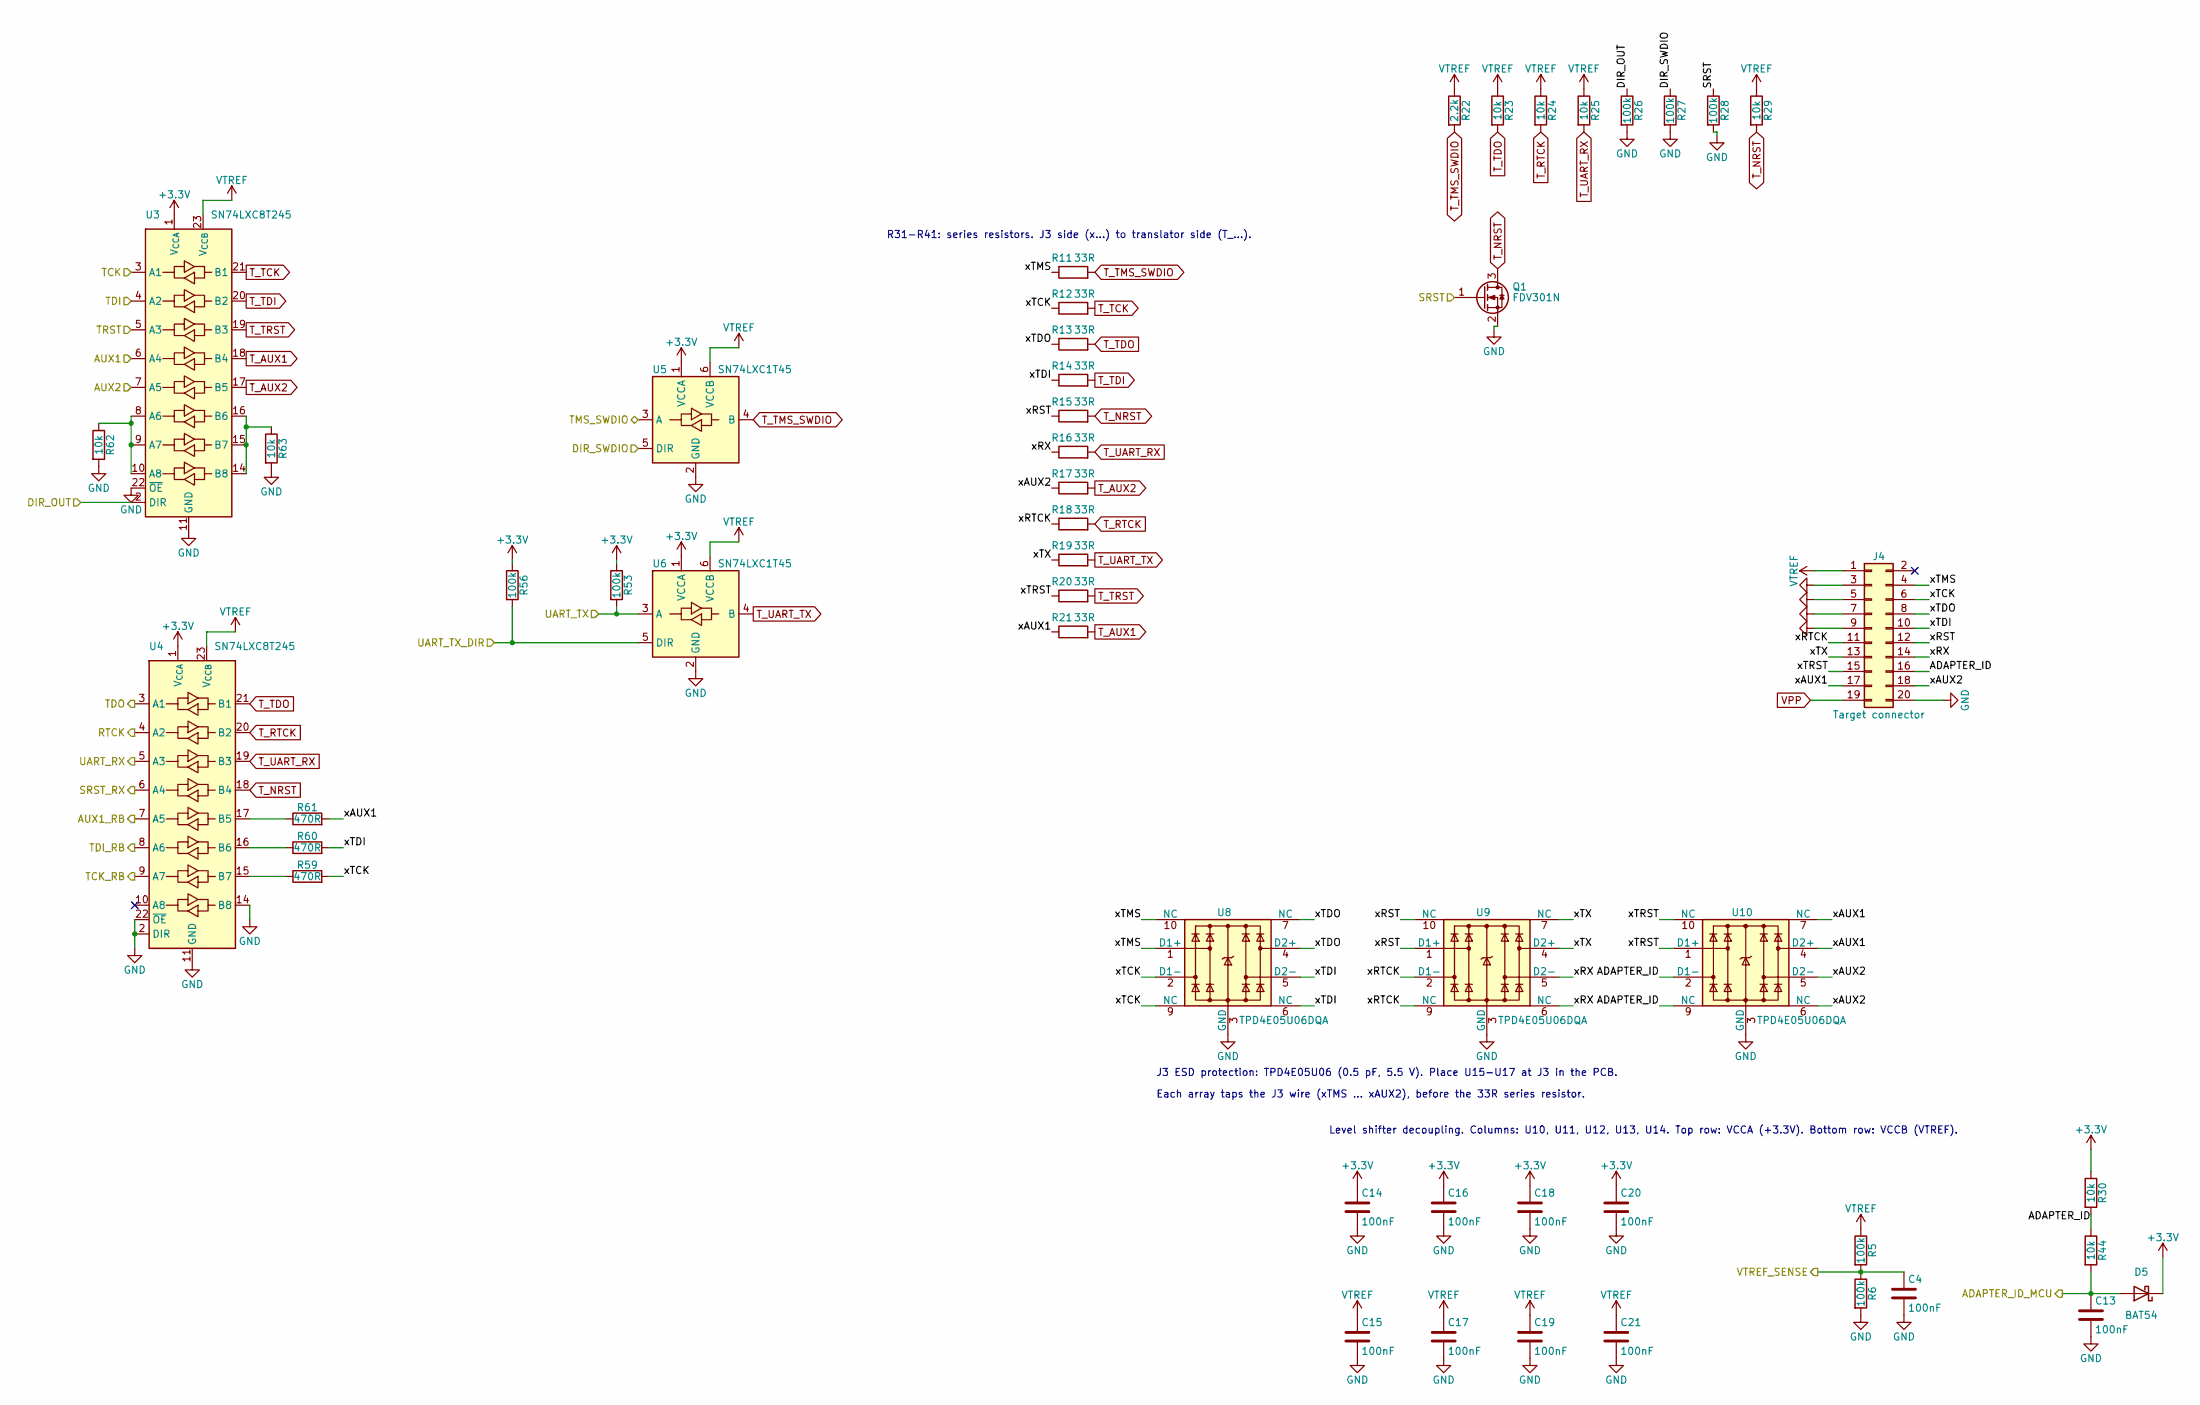
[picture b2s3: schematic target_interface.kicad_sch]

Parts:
C4, C13, C14, C15, C16, C17, C18, C19, C20, C21: 100nF; C_0603; LCSC C14663
D5: BAT54; D_SOD-323; LCSC C21107
J4: Target connector; IDC-Header_2x10_P2.54mm_Horizontal
Q1: FDV301N; SOT-23; LCSC C15310
R5, R6, R26, R27, R28, R53, R56: 100k; R_0402; LCSC C25741
R11, R12, R13, R14, R15, R16, R17, R18, R19, R20, R21: 33R; R_0402; LCSC C25105
R22: 2.2k; R_0402; LCSC C25879
R23, R24, R25, R29, R30, R44, R62, R63: 10k; R_0402; LCSC C25744
R59, R60, R61: 470R; R_0402; LCSC C25117
U3, U4: SN74LXC8T245; TSSOP-24_4.4x7.8mm_P0.65mm; LCSC C4363995
U5, U6: SN74LXC1T45; SOT-23-6; LCSC C4364198
U8, U9, U10: TPD4E05U06DQA; USON-10_2.5x1.0mm_P0.5mm; LCSC C138714

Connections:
/ADAPTER_ID_MCU: C13.1, D5.2 (A), R44.2; also elsewhere on the board
/AUX1: U3.6 (A4); also elsewhere on the board
/AUX1_RB: U4.7 (A5); also elsewhere on the board
/AUX2: U3.7 (A5); also elsewhere on the board
/DIR_OUT: R26.1, U3.2 (DIR); also elsewhere on the board
/DIR_SWDIO: R27.1, U5.5 (DIR); also elsewhere on the board
/RTCK: U4.4 (A2); also elsewhere on the board
/SRST: Q1.1 (G), R28.1; also elsewhere on the board
/SRST_RX: U4.6 (A4); also elsewhere on the board
/TCK_RB: U4.9 (A7); also elsewhere on the board
/TDI: U3.4 (A2); also elsewhere on the board
/TDI_RB: U4.8 (A6); also elsewhere on the board
/TDO: U4.3 (A1); also elsewhere on the board
/TMS_SWDIO: U5.3 (A); also elsewhere on the board
/TRST: U3.5 (A3); also elsewhere on the board
/Target interface/ADAPTER_ID: J4.16, R30.2, R44.1, U10.2 (D1-), U10.9 (NC)
/Target interface/xAUX1: J4.17, R21.1, R61.2, U10.4 (D2+), U10.7 (NC)
/Target interface/xAUX2: J4.18, R17.1, U10.5 (D2-), U10.6 (NC)
/Target interface/xRST: J4.12, R15.1, U9.1 (D1+), U9.10 (NC)
/Target interface/xRTCK: J4.11, R18.1, U9.2 (D1-), U9.9 (NC)
/Target interface/xRX: J4.14, R16.1, U9.5 (D2-), U9.6 (NC)
/Target interface/xTCK: J4.6, R12.1, R59.2, U8.2 (D1-), U8.9 (NC)
/Target interface/xTDI: J4.10, R14.1, R60.2, U8.5 (D2-), U8.6 (NC)
/Target interface/xTDO: J4.8, R13.1, U8.4 (D2+), U8.7 (NC)
/Target interface/xTMS: J4.4, R11.1, U8.1 (D1+), U8.10 (NC)
/Target interface/xTRST: J4.15, R20.1, U10.1 (D1+), U10.10 (NC)
/Target interface/xTX: J4.13, R19.1, U9.4 (D2+), U9.7 (NC)
/UART_RX: U4.5 (A3); also elsewhere on the board
/UART_TX: R53.2, U6.3 (A); also elsewhere on the board
/UART_TX_DIR: R56.2, U6.5 (DIR); also elsewhere on the board
/VTREF_SENSE: C4.1, R5.2, R6.1; also elsewhere on the board
unnamed: R62.1, U3.8 (A6), U3.9 (A7), U3.10 (A8)
unnamed: R63.1, U3.14 (B8), U3.15 (B7), U3.16 (B6)
unnamed: R61.1, U4.17 (B5)
unnamed: R60.1, U4.16 (B6)
unnamed: R59.1, U4.15 (B7)
T_AUX1: R21.2, U3.18 (B4)
T_AUX2: R17.2, U3.17 (B5)
T_NRST: Q1.3 (D), R15.2, R29.2, U4.18 (B4)
T_RTCK: R18.2, R24.2, U4.20 (B2)
T_TCK: R12.2, U3.21 (B1)
T_TDI: R14.2, U3.20 (B2)
T_TDO: R13.2, R23.2, U4.21 (B1)
T_TMS_SWDIO: R11.2, R22.2, U5.4 (B)
T_TRST: R20.2, U3.19 (B3)
T_UART_RX: R16.2, R25.2, U4.19 (B3)
T_UART_TX: R19.2, U6.4 (B)
VPP: J4.19; also elsewhere on the board

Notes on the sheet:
J3 ESD protection: TPD4E05U06 (0.5 pF, 5.5 V). Place U15-U17 at J3 in the PCB.
Each array taps the J3 wire (xTMS ... xAUX2), before the 33R series resistor.
R31-R41: series resistors. J3 side (x...) to translator side (T_...).
Level shifter decoupling. Columns: U10, U11, U12, U13, U14. Top row: VCCA (+3.3V). Bottom row: VCCB (VTREF).

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
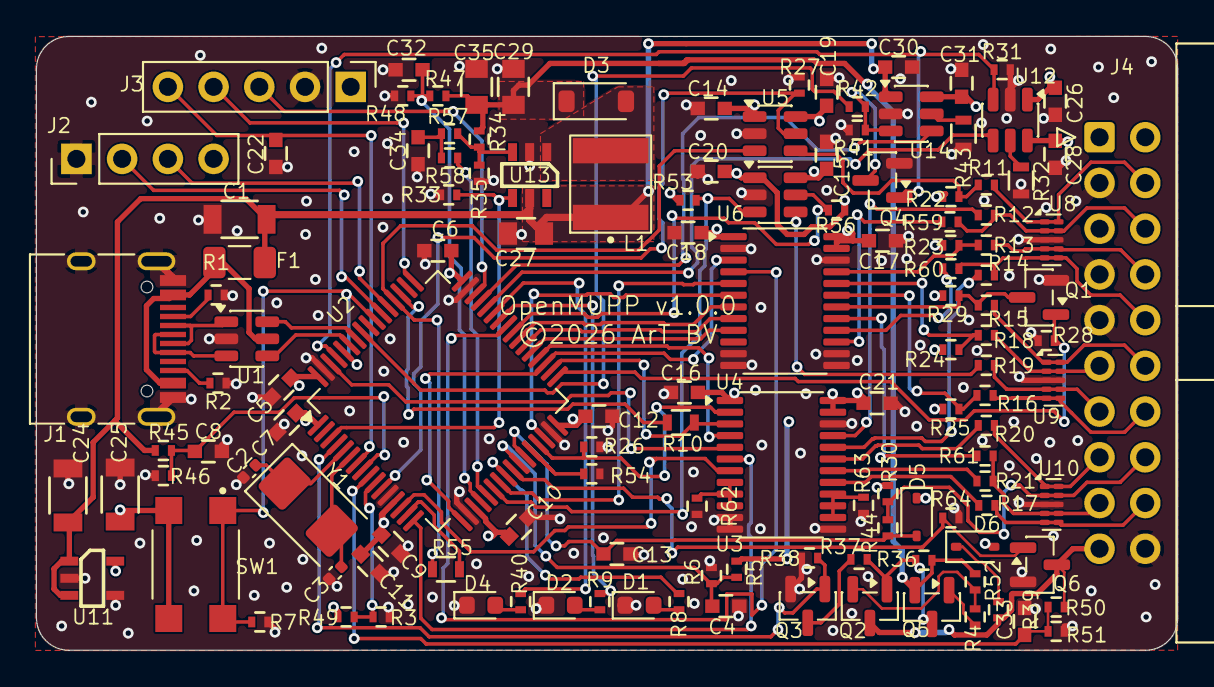
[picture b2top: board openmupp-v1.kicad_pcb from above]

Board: 4 copper layers, 63.4 x 34.1 mm, 131 parts (0 on the bottom side), 101 nets.

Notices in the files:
openmupp-v1.kicad_pcb:
©2026 ArT BV
parts and their libraries:
copyright: 2018 Armin van der Togt
